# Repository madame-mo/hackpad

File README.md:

# mo's hackpad
This hackpad is my first electronics project! I love the world of electronics and embedded software engineering, and I really wanted to get my hands dirty making my first project as part of my 2026 goals. Now I can say that in just the first week of 2026, I've made my very first PCB (which I'm super proud of!). This is all thanks to Blueprint via Hackpad :) yayy!

## Features
- 7 Keys, 1 top key for toggling settings (hopefully a feature I will add in the future)
- 1 Rotary Encoder for any usage
- 3 LED's

## PCB
My PCB was made in KiCad, had a few issues routing the LED's.

PCB Schematic 
<div></div>

PCB 
<div></div>

*And here's how the PCB will look once made
<div></div>

## CAD
The 3D model of my Hackpad case was made in Onshape since I had a few issues installing Fusion360.

Hackpad Case 3D Model 
<div></div>

## Firmware

The firmware is pretty basic, using KMK firmware. I plan to update it in the future as I get better with electronics and embedded software engineering.

## BOM
- 1x XIAO RP2040
- 1x EC11 Rotary Encoder
- 7x Cherry MX Switches
- 1x Case (2 printed parts)
- 3x SKIMINI-E LEDs

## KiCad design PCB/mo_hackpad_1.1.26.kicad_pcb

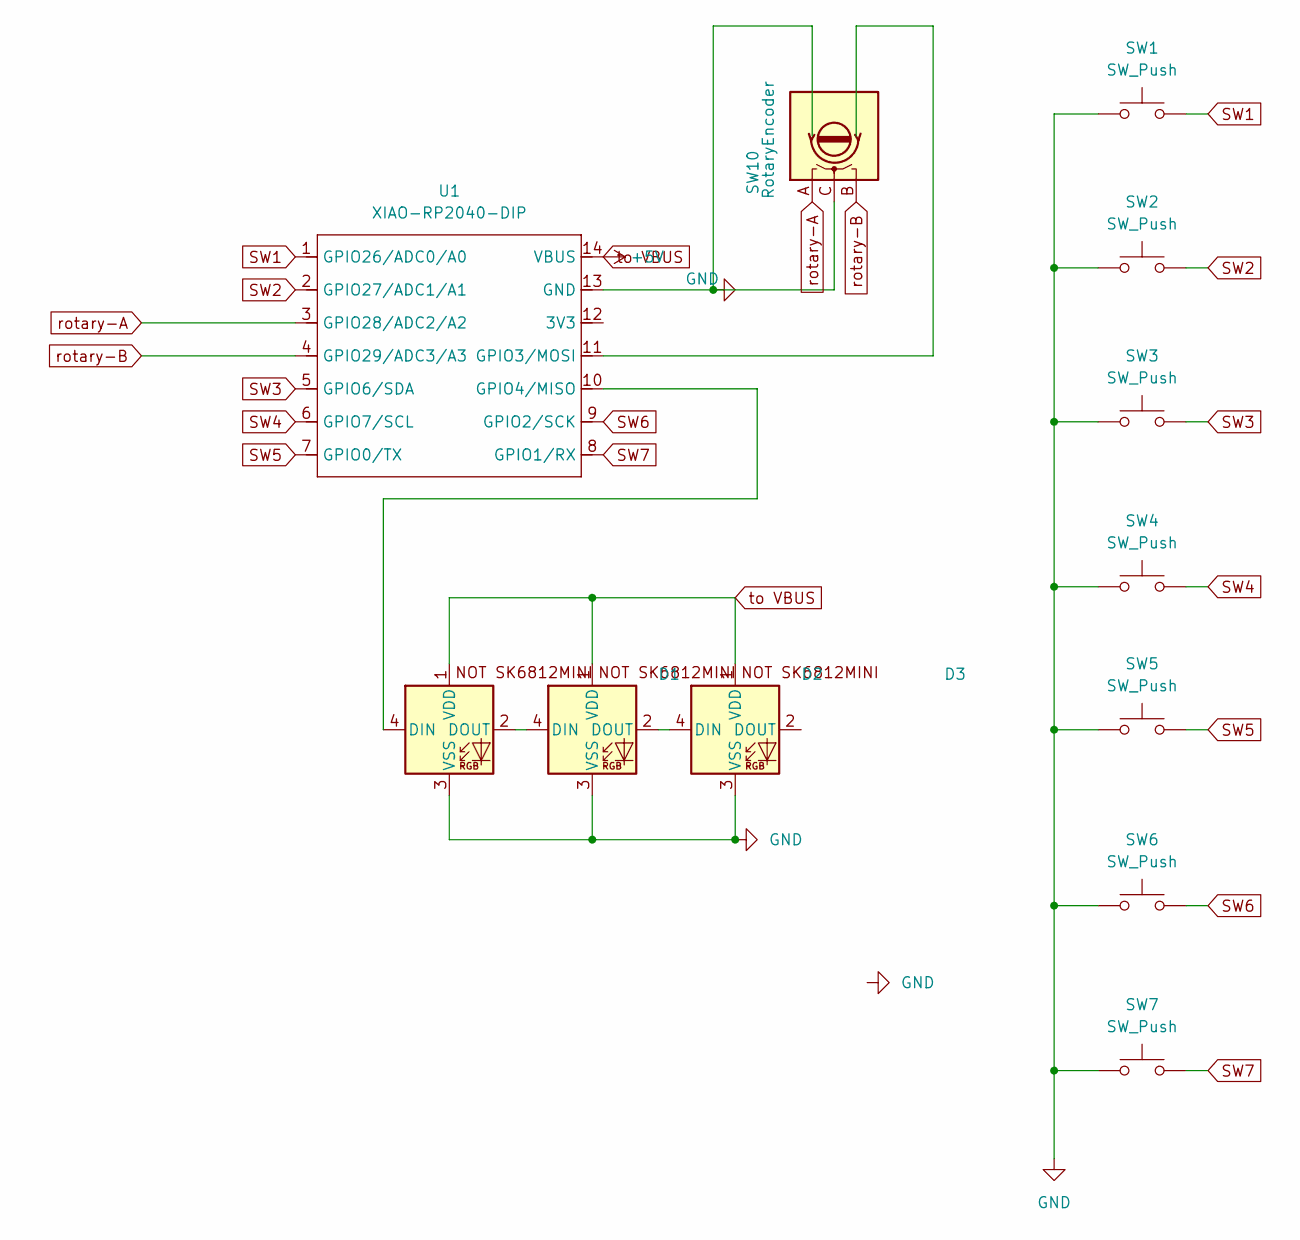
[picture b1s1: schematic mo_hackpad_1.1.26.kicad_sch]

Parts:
D1, D2, D3: SK6812MINI-E; SK6812MINI-E_fixed
SW1, SW2, SW3, SW4, SW5, SW6, SW7: SW_Push; SW_Cherry_MX_1.00u_PCB
SW10: RotaryEncoder; RotaryEncoder_Alps_EC11E-Switch_Vertical_H20mm
U1: XIAO-RP2040-DIP

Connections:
GND: D1.3 (VSS), D2.3 (VSS), D3.3 (VSS), SW1.1, SW2.1, SW3.1, SW4.1, SW5.1, SW6.1, SW7.1, SW10.C, U1.13 (GND)
unnamed: D1.4 (DIN), U1.10 (GPIO4/MISO)
unnamed: D1.2 (DOUT), D2.4 (DIN)
unnamed: D2.2 (DOUT), D3.4 (DIN)
SW1: SW1.2, U1.1 (GPIO26/ADC0/A0)
SW2: SW2.2, U1.2 (GPIO27/ADC1/A1)
SW3: SW3.2, U1.5 (GPIO6/SDA)
SW4: SW4.2, U1.6 (GPIO7/SCL)
SW5: SW5.2, U1.7 (GPIO0/TX)
SW6: SW6.2, U1.9 (GPIO2/SCK)
SW7: SW7.2, U1.8 (GPIO1/RX)
rotary-A: SW10.A, U1.3 (GPIO28/ADC2/A2)
rotary-B: SW10.B, U1.4 (GPIO29/ADC3/A3)
to VBUS: D1.1 (VDD), D2.1 (VDD), D3.1 (VDD), U1.14 (VBUS)

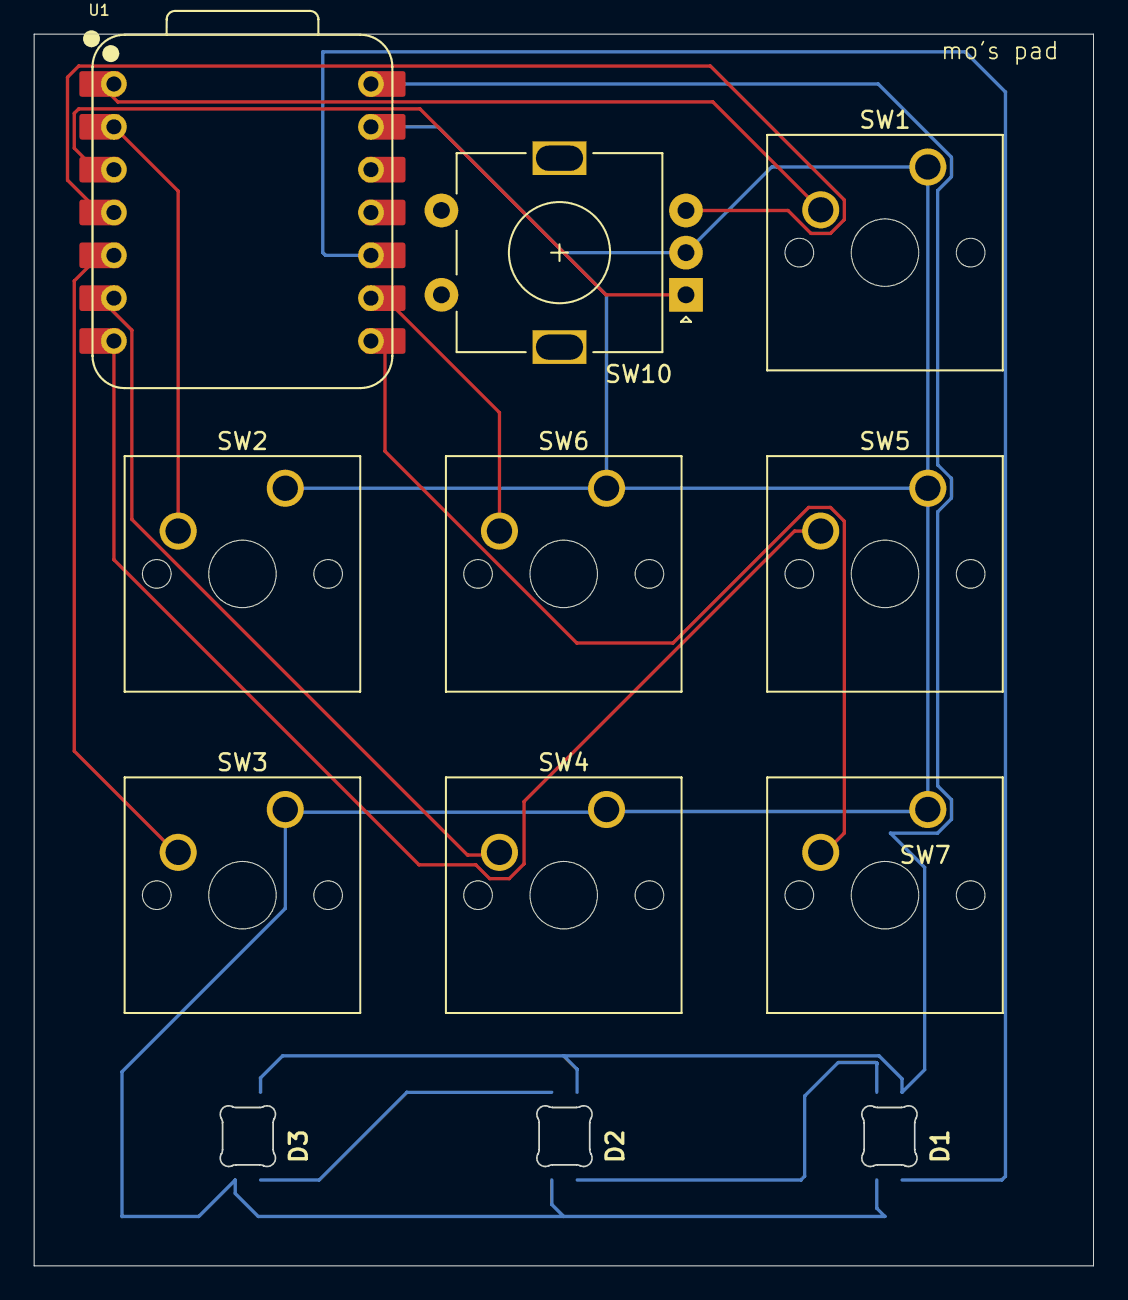
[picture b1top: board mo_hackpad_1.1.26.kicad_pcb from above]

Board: 2 copper layers, 62.8 x 73.0 mm, 12 parts (0 on the bottom side), 14 nets.

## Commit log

2026-01-03 KiCad files, uploaded PCB design
2026-01-03 created directory for pcb
2026-01-03 added to PCB folder
2026-01-03 create repo for images
2026-01-03 add images of hackpad
    3d, wiring, and schematic
2026-01-04 img file
2026-01-04 added updated images for hackpad pcb
2026-01-15 Create DELETE
2026-01-15 PCB files
2026-01-15 Create DELETEME
2026-01-16 Create DELETETHIS
2026-01-18 Create dletethis
2026-01-18 Rename README.jpg to 3d_pcb.jpg
2026-01-19 add images of PCB/Hackpad
2026-01-19 Add width to images in README.md
2026-01-19 Format images section in README.md
2026-01-19 Wrap images in div tags for improved layout
    Updated image tags to use div wrappers for better formatting.
2026-01-19 Revise README with project overview and specifications
    Updated project details and added sections for features, PCB, CAD, firmware, and BOM.
2026-01-19 Fix formatting and section headers in README.md
    Corrected formatting and spacing in the README sections.
2026-01-19 Replace PCB schematic image with a new version
    Updated PCB images in the README file.
2026-01-20 uploaded updated PCB
    fixed issues with the Rotary Encoder, changed from RotaryEncoder to RotaryEncoder_Switch to be able to use switch pins.
2026-01-20 Update PCB and CAD images in README
    Updated images in the README to reflect new schematic and PCB designs.
2026-01-20 Update image source for Hackpad case 3D model
2026-01-20 Update README with PCB image and firmware details
    Added an image of the PCB's final appearance and updated the firmware section.
2026-01-20 Add width attribute to PCB image in README
    Updated image tag in README to include width attribute.
